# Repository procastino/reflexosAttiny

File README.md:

# reflexosAttiny
What can you do with three leds and a button? This is a very unflexible development board, where you must stretch your imagination to take some utility out of it. It has an attiny, the pushbutton and three leds. I left one pin free and accesible, because I'm a twisted guy with some goodness inside.
The real point of this was learning to design a simple board with KiCad and give some use to a bunch of AtTinys that I had laying around. Now I think it has some interest, for the right kind of people...
## Board
Develped in Kicad 4 (I'll upgrade if I beat my determined lazyness), it is surely not correct from a technical point of view, but it seems to work well.
## BOM
* 1 x AtTiny 85 - 20PU
* 1 x pushbutton 6 mm
* 3 x leds 3 mm
* 3 x 470 ohm resistors (depending on the leds, may need different value)
* 1 x 10Kohm resistor
* 12 right angle male pin headers
* 1 x cr2032 battery holder
* 1 x switch SK12D07V-G3

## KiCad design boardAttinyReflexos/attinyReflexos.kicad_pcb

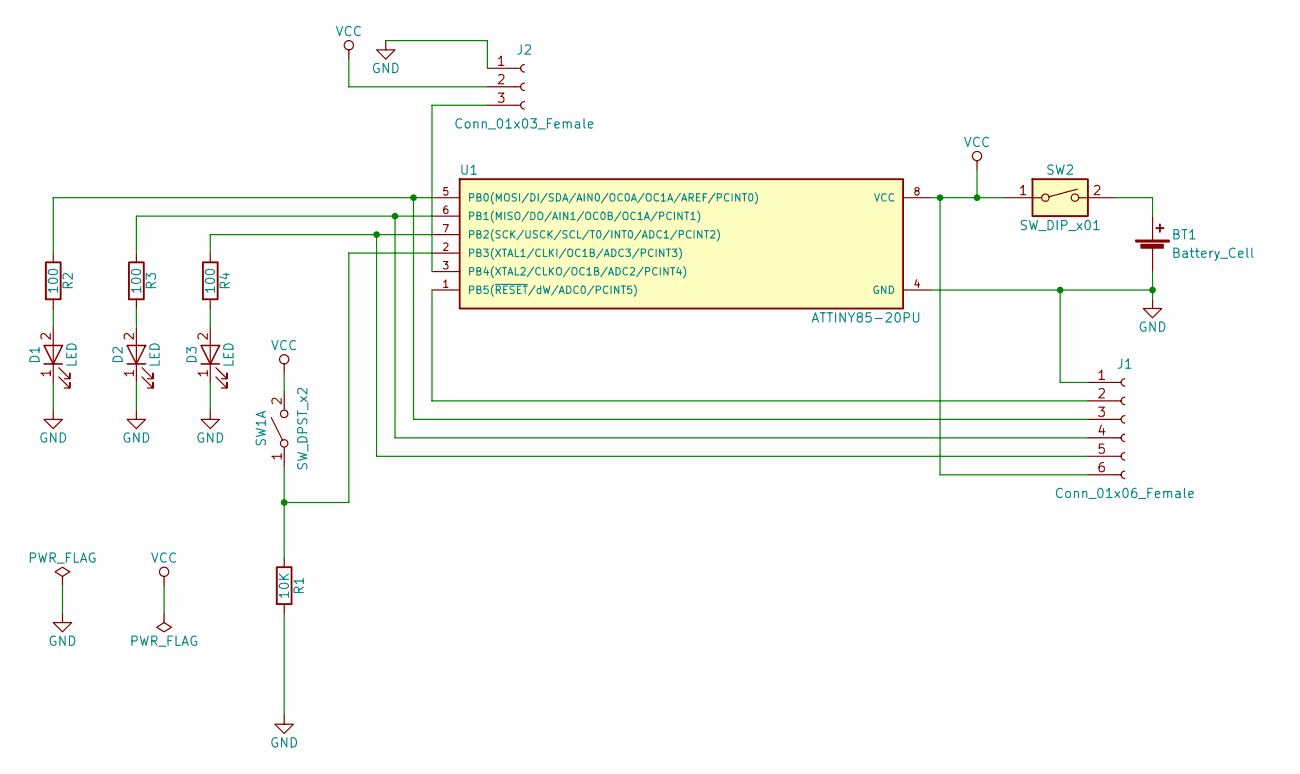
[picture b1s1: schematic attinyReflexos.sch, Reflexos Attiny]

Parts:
BT1: Battery_Cell; Keystone_103_1x20mm-CoinCell
D1, D2, D3: LED; LED_D3.0mm
J1: Conn_01x06_Female; Pin_Header_Angled_1x06_Pitch2.54mm
J2: Conn_01x03_Female; Pin_Header_Angled_1x03_Pitch2.54mm
R1: 10K; R_Axial_DIN0207_L6.3mm_D2.5mm_P7.62mm_Horizontal
R2, R3, R4: 100; R_Axial_DIN0207_L6.3mm_D2.5mm_P7.62mm_Horizontal
SW1: SW_DPST_x2; SW_PUSH_6mm_H5mm
SW2: SW_DIP_x01; switchSlide
U1: ATTINY85-20PU; DIP-8_W7.62mm

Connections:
GND: BT1.2 (-), D1.1 (K), D2.1 (K), D3.1 (K), J1.1, J2.1, R1.2, U1.4 (GND)
unnamed: BT1.1 (+), SW2.2
unnamed: D1.2 (A), R2.2
unnamed: D2.2 (A), R3.2
unnamed: D3.2 (A), R4.2
unnamed: J1.2, U1.1 (PB5(~RESET~/dW/ADC0/PCINT5))
unnamed: J1.3, R2.1, U1.5 (PB0(MOSI/DI/SDA/AIN0/OC0A/OC1A/AREF/PCI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)
unnamed: J1.4, R3.1, U1.6 (PB1(MISO/DO/AIN1/OC0B/OC1A/PCINT1))
unnamed: J1.5, R4.1, U1.7 (PB2(SCK/USCK/SCL/T0/INT0/ADC1/PCINT2))
unnamed: J2.3, U1.3 (PB4(XTAL2/CLKO/OC1B/ADC2/PCINT4))
unnamed: R1.1, SW1.1 (A), U1.2 (PB3(XTAL1/CLKI/OC1B/ADC3/PCINT3))
VCC: J1.6, J2.2, SW1.2 (B), SW2.1, U1.8 (VCC)

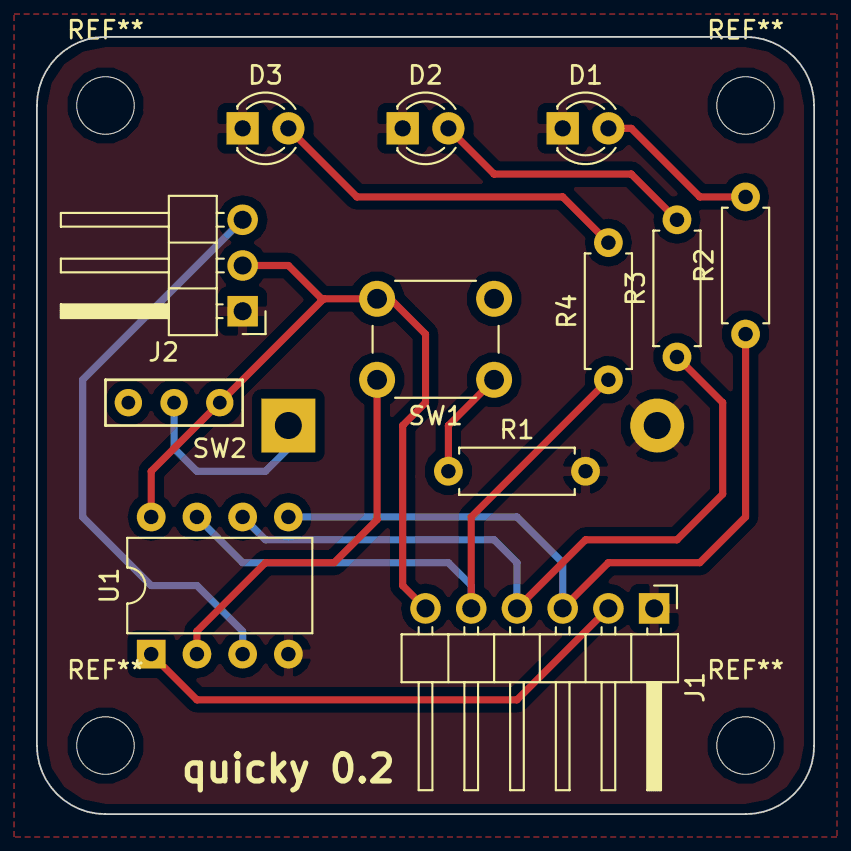
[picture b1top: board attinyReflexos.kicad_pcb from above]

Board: 2 copper layers, 43.2 x 43.2 mm, 13 parts (1 on the bottom side), 12 nets.

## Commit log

2017-10-07 commit inicial
2018-05-23 board files added
2018-05-23 gerber zip added
2018-06-06 corrixido erro
2018-06-13 ancho pistas e buratos
2018-06-14 esquema e pistas anchas
2018-07-01 corrixido bug Serial
2018-07-01 corr bits puntos
2018-09-28 big updates
2018-09-29 better readme
2018-10-26 true randomness
2018-12-16 caixa en openscad

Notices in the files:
boardAttinyReflexos/attinyReflexos.kicad_pcb:
cc-by-sa: tucho mendez
